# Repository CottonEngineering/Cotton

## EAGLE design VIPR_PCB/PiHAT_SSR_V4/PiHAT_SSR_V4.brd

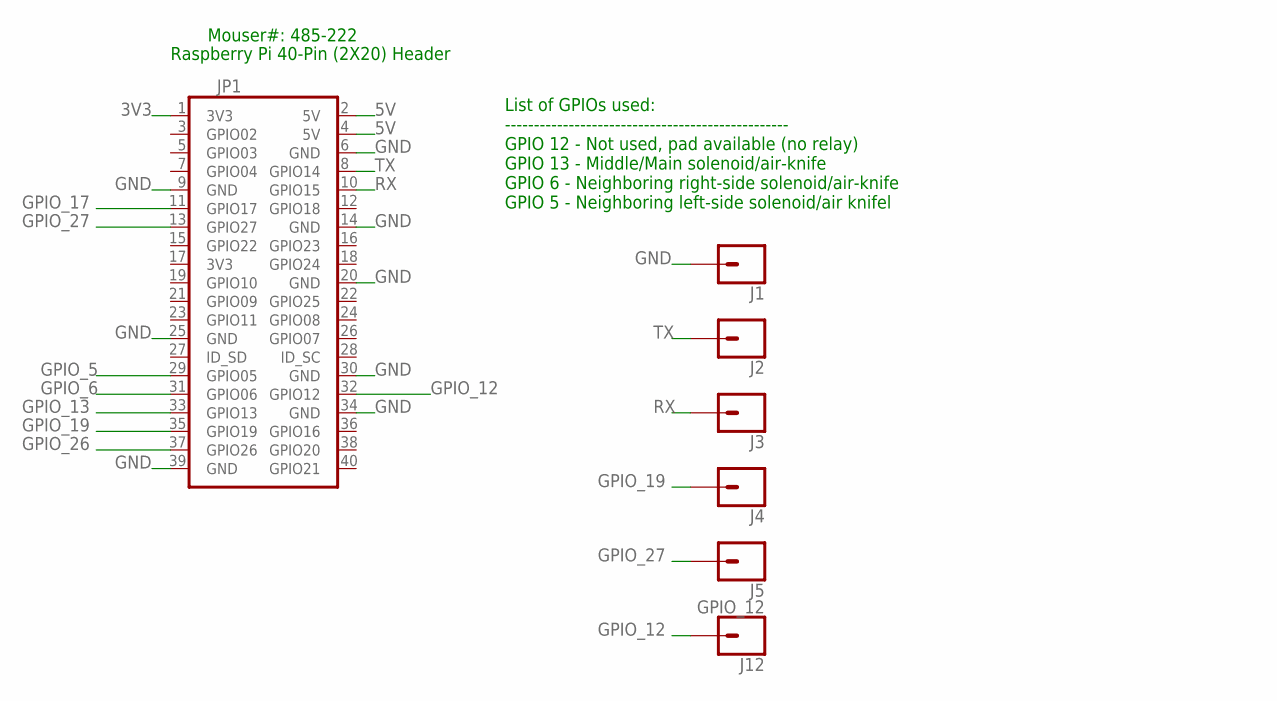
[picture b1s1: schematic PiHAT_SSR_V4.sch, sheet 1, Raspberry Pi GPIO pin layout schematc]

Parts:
J1, J2, J3, J4, J5: CONN_01; 1X01
J12: GPIO_12; 1X01
JP1: 40W_PI_HAT_TPH; 2X20

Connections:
3V3: JP1.1 (3V3); also elsewhere on the board
5V: JP1.2 (5V), JP1.4 (5V); also elsewhere on the board
GND: J1.1, JP1.6 (GND), JP1.9 (GND), JP1.14 (GND), JP1.20 (GND), JP1.25 (GND), JP1.30 (GND), JP1.34 (GND), JP1.39 (GND); also elsewhere on the board
GPIO_5: JP1.29 (GPIO05); also elsewhere on the board
GPIO_6: JP1.31 (GPIO06); also elsewhere on the board
GPIO_12: J12.1, JP1.32 (GPIO12)
GPIO_13: JP1.33 (GPIO13); also elsewhere on the board
GPIO_17: JP1.11 (GPIO17); also elsewhere on the board
GPIO_19: J4.1, JP1.35 (GPIO19)
GPIO_26: JP1.37 (GPIO26)
GPIO_27: J5.1, JP1.13 (GPIO27)
RX: J3.1, JP1.10 (GPIO15)
TX: J2.1, JP1.8 (GPIO14)

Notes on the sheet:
Raspberry Pi 40-Pin (2X20) Header
List of GPIOs used: ------------------------------------------------- GPIO 12 - Not used, pad available (no relay) GPIO 13 - Middle/Main solenoid/air-knife GPIO 6 - Neighboring right-side solenoid/air-knife GPIO 5 - Neighboring left-side solenoid/air knifel
Mouser#: 485-222

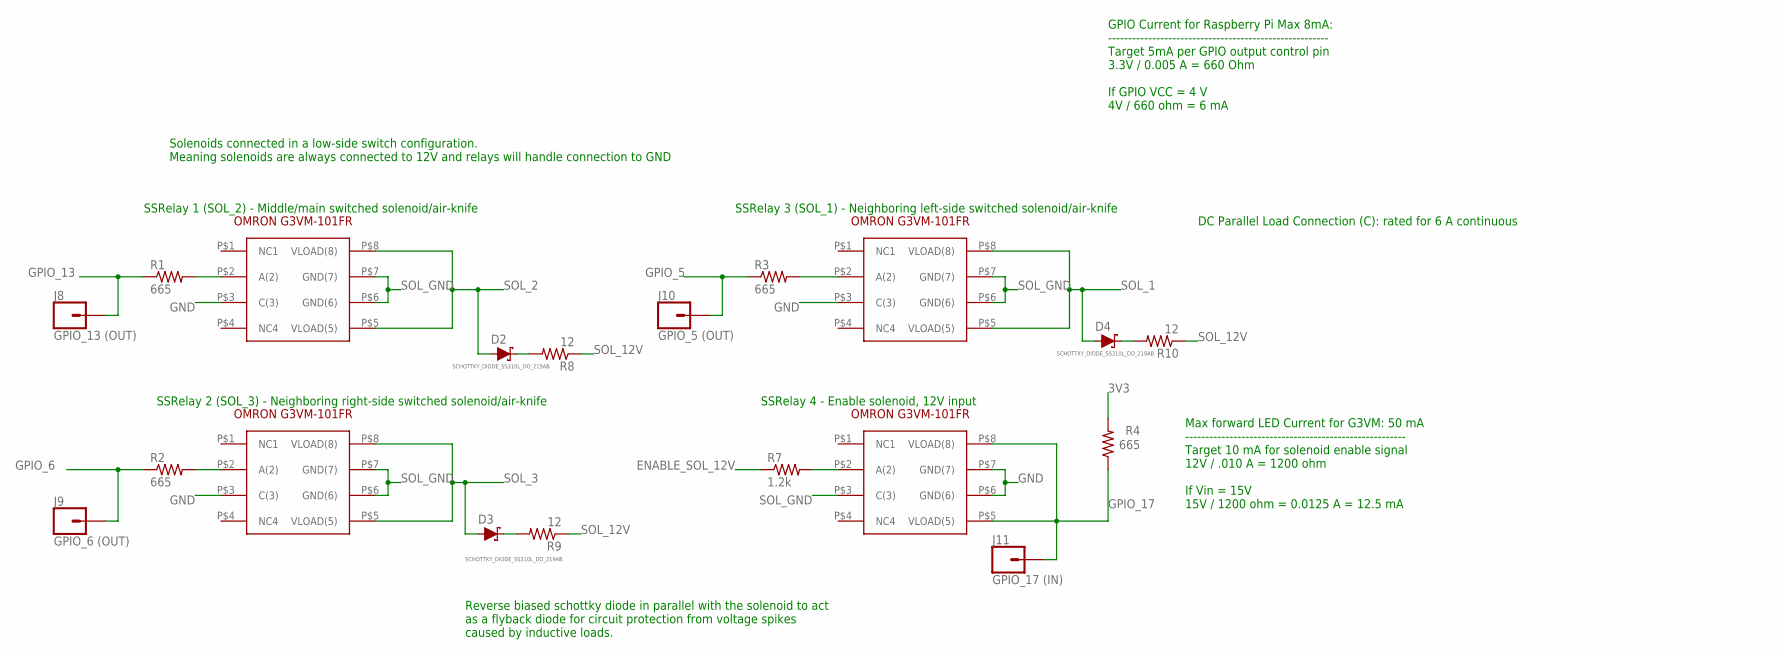
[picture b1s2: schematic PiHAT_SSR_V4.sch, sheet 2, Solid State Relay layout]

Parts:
D2, D3, D4: SCHOTTKY_DIODE_SS310L_DO_219AB; SCHOTTKY_DIODE_DO219AB
J8: GPIO_13 (OUT); 1X01
J9: GPIO_6 (OUT); 1X01
J10: GPIO_5 (OUT); 1X01
J11: GPIO_17 (IN); 1X01
R1, R2, R3, R4: 665; M0805
R7: 1.2k; M0805
R8, R9, R10: 12; R1210
SSR1, SSR2, SSR3, SSR4: OMRON_G3VM_101FR; OMRON_G3VM-101FR

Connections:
3V3: R4.2; also elsewhere on the board
ENABLE_SOL_12V: R7.1; also elsewhere on the board
GND: SSR1.P$3 (C(3)), SSR2.P$3 (C(3)), SSR3.P$3 (C(3)), SSR4.P$6 (GND(6)), SSR4.P$7 (GND(7)); also elsewhere on the board
GPIO_5: J10.1, R3.1; also elsewhere on the board
GPIO_6: J9.1, R2.1; also elsewhere on the board
GPIO_13: J8.1, R1.1; also elsewhere on the board
GPIO_17: J11.1, R4.1, SSR4.P$5 (VLOAD(5)), SSR4.P$8 (VLOAD(8)); also elsewhere on the board
unnamed: D2.P$2 (C), R8.2
unnamed: R3.2, SSR3.P$2 (A(2))
unnamed: D3.P$2 (C), R9.2
unnamed: R2.2, SSR2.P$2 (A(2))
unnamed: R1.2, SSR1.P$2 (A(2))
unnamed: R7.2, SSR4.P$2 (A(2))
unnamed: D4.P$2 (C), R10.2
SOL_1: D4.P$1 (A), SSR3.P$5 (VLOAD(5)), SSR3.P$8 (VLOAD(8)); also elsewhere on the board
SOL_2: D2.P$1 (A), SSR1.P$5 (VLOAD(5)), SSR1.P$8 (VLOAD(8)); also elsewhere on the board
SOL_3: D3.P$1 (A), SSR2.P$5 (VLOAD(5)), SSR2.P$8 (VLOAD(8)); also elsewhere on the board
SOL_12V: R8.1, R9.1, R10.1; also elsewhere on the board
SOL_GND: SSR1.P$6 (GND(6)), SSR1.P$7 (GND(7)), SSR2.P$6 (GND(6)), SSR2.P$7 (GND(7)), SSR3.P$6 (GND(6)), SSR3.P$7 (GND(7)), SSR4.P$3 (C(3)); also elsewhere on the board

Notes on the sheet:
SSRelay 2 (SOL_3) - Neighboring right-side switched solenoid/air-knife
SSRelay 1 (SOL_2) - Middle/main switched solenoid/air-knife
SSRelay 3 (SOL_1) - Neighboring left-side switched solenoid/air-knife
SSRelay 4 - Enable solenoid, 12V input
GPIO Current for Raspberry Pi Max 8mA: ------------------------------------------------------- Target 5mA per GPIO output control pin 3.3V / 0.005 A = 660 Ohm If GPIO VCC = 4 V 4V / 660 ohm = 6 mA
Max forward LED Current for G3VM: 50 mA ------------------------------------------------------- Target 10 mA for solenoid enable signal 12V / .010 A = 1200 ohm If Vin = 15V 15V / 1200 ohm = 0.0125 A = 12.5 mA
DC Parallel Load Connection (C): rated for 6 A continuous
Solenoids connected in a low-side switch configuration. Meaning solenoids are always connected to 12V and relays will handle connection to GND
Reverse biased schottky diode in parallel with the solenoid to act as a flyback diode for circuit protection from voltage spikes caused by inductive loads.

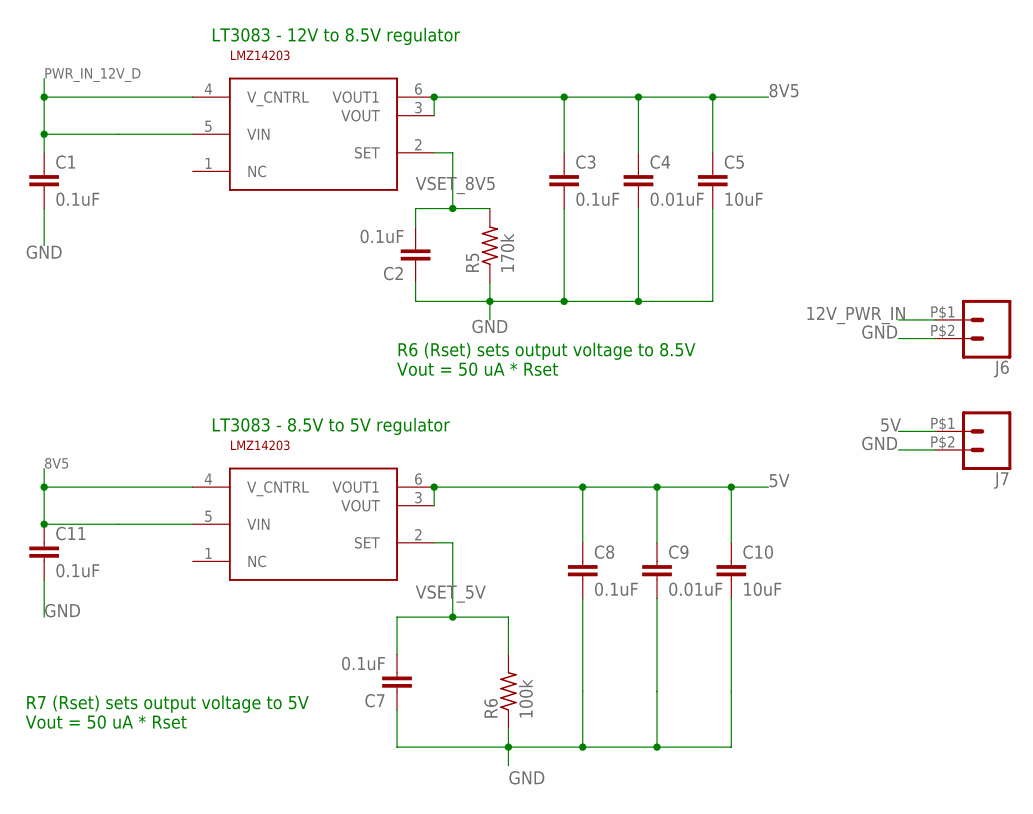
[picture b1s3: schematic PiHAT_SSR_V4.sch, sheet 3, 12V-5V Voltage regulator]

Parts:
C1, C2, C3, C7, C8, C11: 0.1uF; C0805
C4, C9: 0.01uF; C0805
C5, C10: 10uF; C0805
J6, J7: CONN_02PTH2; 1X02_BIG
R5: 170k; M0805
R6: 100k; M0805
VR1, VR2: SMD-SPECIAL_28PIN_PIC32_11_3_2011_LT3083; SMD-SPECIAL_28PIN_PIC32_11_3_2011_DPAK-5

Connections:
5V: C8.1, C9.1, C10.1, J7.P$1 (1), VR2.3 (VOUT), VR2.6 (VOUT1); also elsewhere on the board
8V5: C3.1, C4.1, C5.1, C11.1, VR1.3 (VOUT), VR1.6 (VOUT1), VR2.4 (V_CNTRL), VR2.5 (VIN)
12V_PWR_IN: J6.P$1 (1); also elsewhere on the board
GND: C1.2, C2.1, C3.2, C4.2, C5.2, C7.1, C8.2, C9.2, C10.2, C11.2, J6.P$2 (2), J7.P$2 (2), R5.1, R6.1; also elsewhere on the board
PWR_IN_12V_D: C1.1, VR1.4 (V_CNTRL), VR1.5 (VIN); also elsewhere on the board
VSET_5V: C7.2, R6.2, VR2.2 (SET)
VSET_8V5: C2.2, R5.2, VR1.2 (SET)

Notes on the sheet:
LT3083 - 12V to 8.5V regulator
R6 (Rset) sets output voltage to 8.5V Vout = 50 uA * Rset
LT3083 - 8.5V to 5V regulator
R7 (Rset) sets output voltage to 5V Vout = 50 uA * Rset

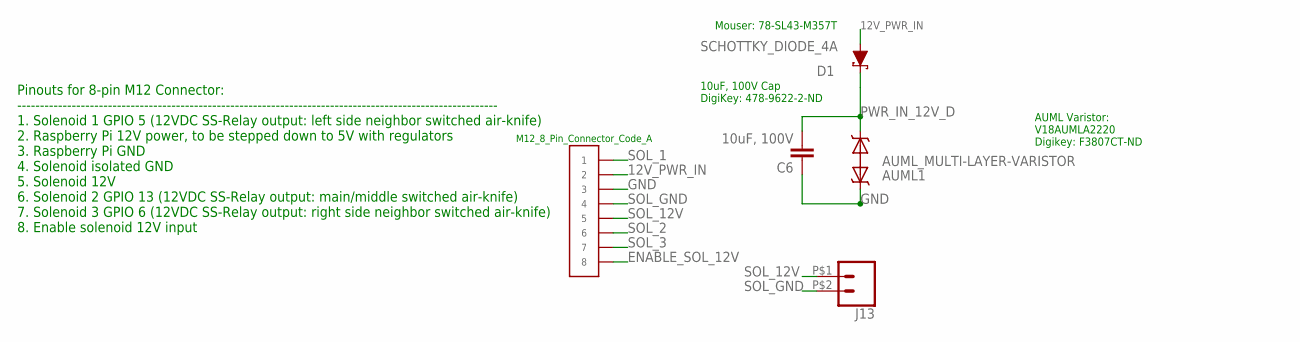
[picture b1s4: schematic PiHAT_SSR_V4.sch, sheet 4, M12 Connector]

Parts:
AUML1: SMD-SPECIAL_28PIN_PIC32_11_3_2011_MOD5_20_13_AUML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; SMD-SPECIAL_28PIN_PIC32_11_3_2011_MOD5_20_13_SMT_CAP_2220
C6: 10uF, 100V; C2220K
CN1: M12_8PIN_CODE_A
D1: SCHOTTKY_DIODE_4A; SCHOTTKY_DIODE_SMD_DO-214AB
J13: CONN_02PTH2; 1X02_BIG

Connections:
12V_PWR_IN: CN1.P$2, D1.P$2 (A); also elsewhere on the board
ENABLE_SOL_12V: CN1.P$8; also elsewhere on the board
GND: AUML1.1, C6.1, CN1.P$3; also elsewhere on the board
PWR_IN_12V_D: AUML1.2, C6.2, D1.P$1 (C); also elsewhere on the board
SOL_1: CN1.P$1; also elsewhere on the board
SOL_2: CN1.P$6; also elsewhere on the board
SOL_3: CN1.P$7; also elsewhere on the board
SOL_12V: CN1.P$5, J13.P$1 (1); also elsewhere on the board
SOL_GND: CN1.P$4, J13.P$2 (2); also elsewhere on the board

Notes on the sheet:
Pinouts for 8-pin M12 Connector: ---------------------------------------------------------------------------------------------------------- 1. Solenoid 1 GPIO 5 (12VDC SS-Relay output: left side neighbor switched air-knife) 2. Raspberry Pi 12V power, to be stepped down to 5V with regulators 3. Rasp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
AUML_MULTI-LAYER-VARISTOR
10uF, 100V Cap DigiKey: 478-9622-2-ND
AUML Varistor: V18AUMLA2220 Digikey: F3807CT-ND
Mouser: 78-SL43-M357T

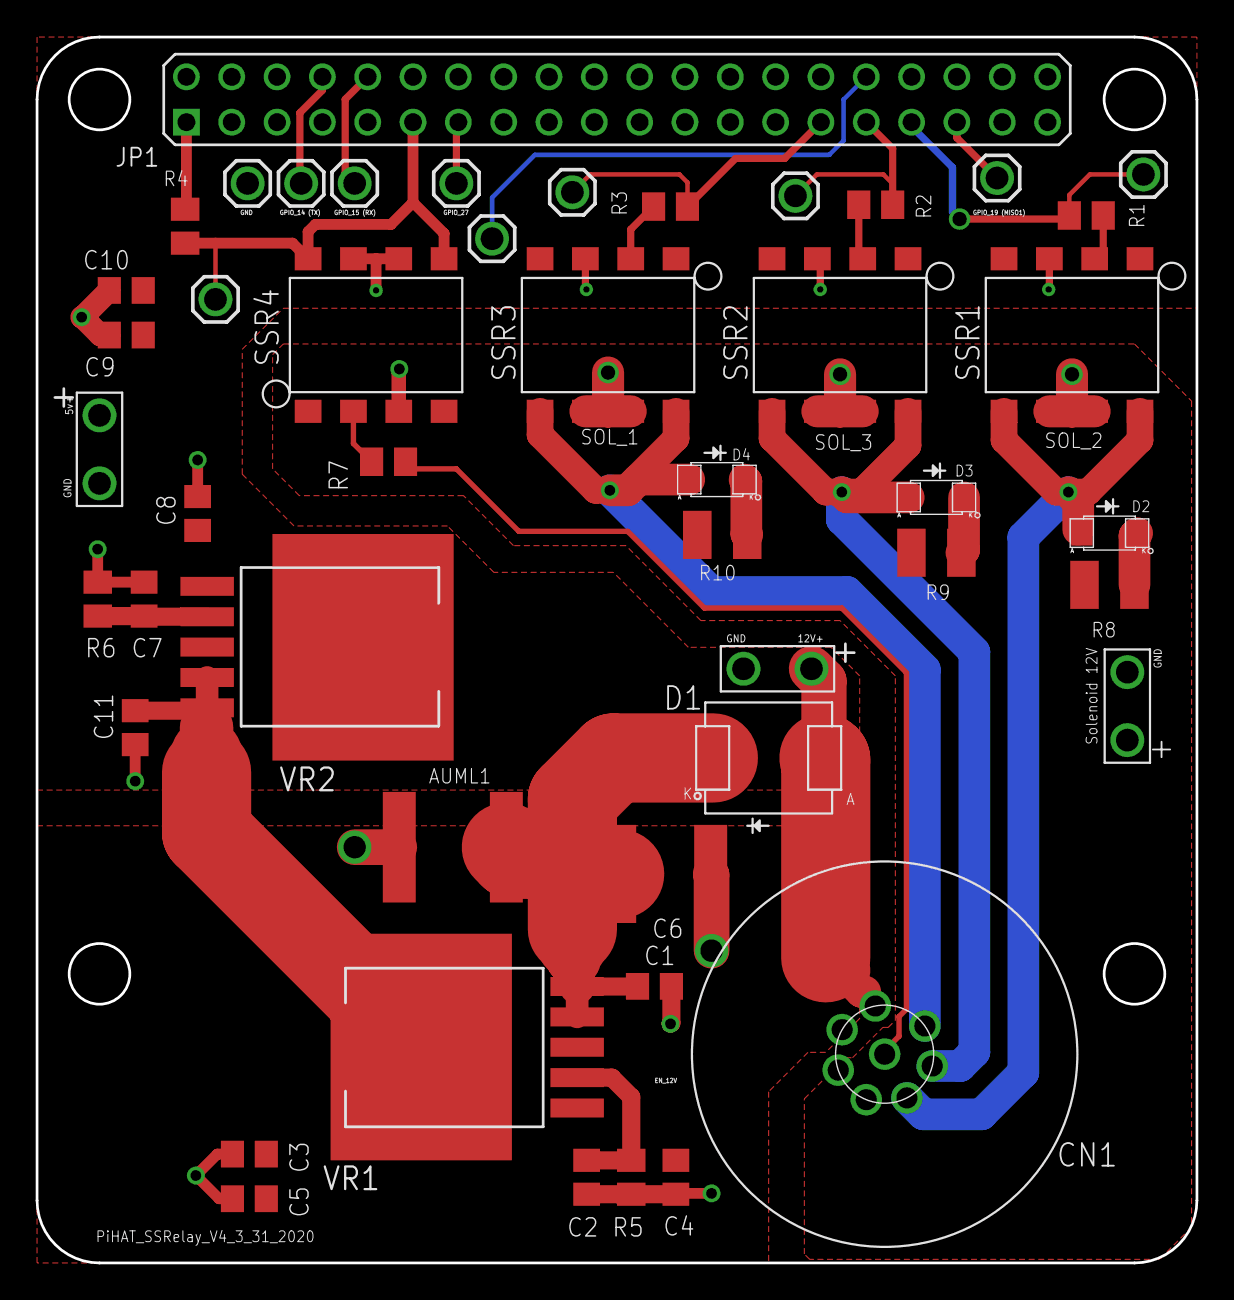
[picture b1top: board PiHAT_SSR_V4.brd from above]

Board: 2 copper layers, 65.0 x 68.7 mm, 47 parts (0 on the bottom side), 30 nets.
